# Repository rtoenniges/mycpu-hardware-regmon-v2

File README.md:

# MyCPU_HDW_RegMonV2
A hardware expansion for for the [MyCPU](http://www.mycpu.eu/) from Dennis Kuschel to display the various CPU internal registers.

#### Attention: 
**This project especially the layouts are not yet finished and have _never been tested!_
So be careful if you connect this to your MyCPU!**

## Features
- Values display in Hex using an EPROM to convert Binary to 7-segment
- Hold CPU on a specific address using DIP-Switches
- You dont have to build the whole Monitor - Its split into 3x Driver and 2x Monitor modules

## Registers
- Accu
- X-Reg
- Y-Reg
- Stackpointer
- OP-Code
- ALU-Reg 1
- ALU-Reg 2
- ALU-OUT
- Sign-, Zero-, Carry-Flag
- Program Counter
- Addressregister

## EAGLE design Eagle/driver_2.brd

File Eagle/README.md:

# Hardware (Drivers and Monitors)
The hardware is each splitted into two modules (Driver and Monitor).
The two modules where connected by a ribbon cable which should not be too long.

## Driver 1 (Program Counter) -> Monitor 12
Driver 1 is for the Program Counter and have to be placed between the Signal Decoder- and the Program Counter-Board.

You have to remove IC44 and IC46 from the Program-Counter-Board and place it on the Driver 1-Board and use IC socket extensions to connect the ICs again to the Programm Counter-Board like the Memory-Base-, and the Memory-Extension-Board.

You can connect the Monitor 12-Board to display the Programm Counter value.

## Driver 2 (Address Bus) -> Monitor 12, AddressHold
Driver 2 is for the Address Bus and have to be placed between the Program Counter- and the Bus Interface-Board

You can connect the Monitor 12-Board to display the Address Bus value and with the AddressHold-Board you can select an address with dip-switches to hold the CPU on a specific point.

## Driver 3 (Accu, X, Y, SP, OP, AR1, AR2, ALU, O-, V-, C-Flag) -> Monitor 3
Driver 3 is for the various internal CPU register and have to be placed between the Microcode Control- and the Signal Decoder-Board.

You can connect the Monitor 3-Board to display all the registers and flags.

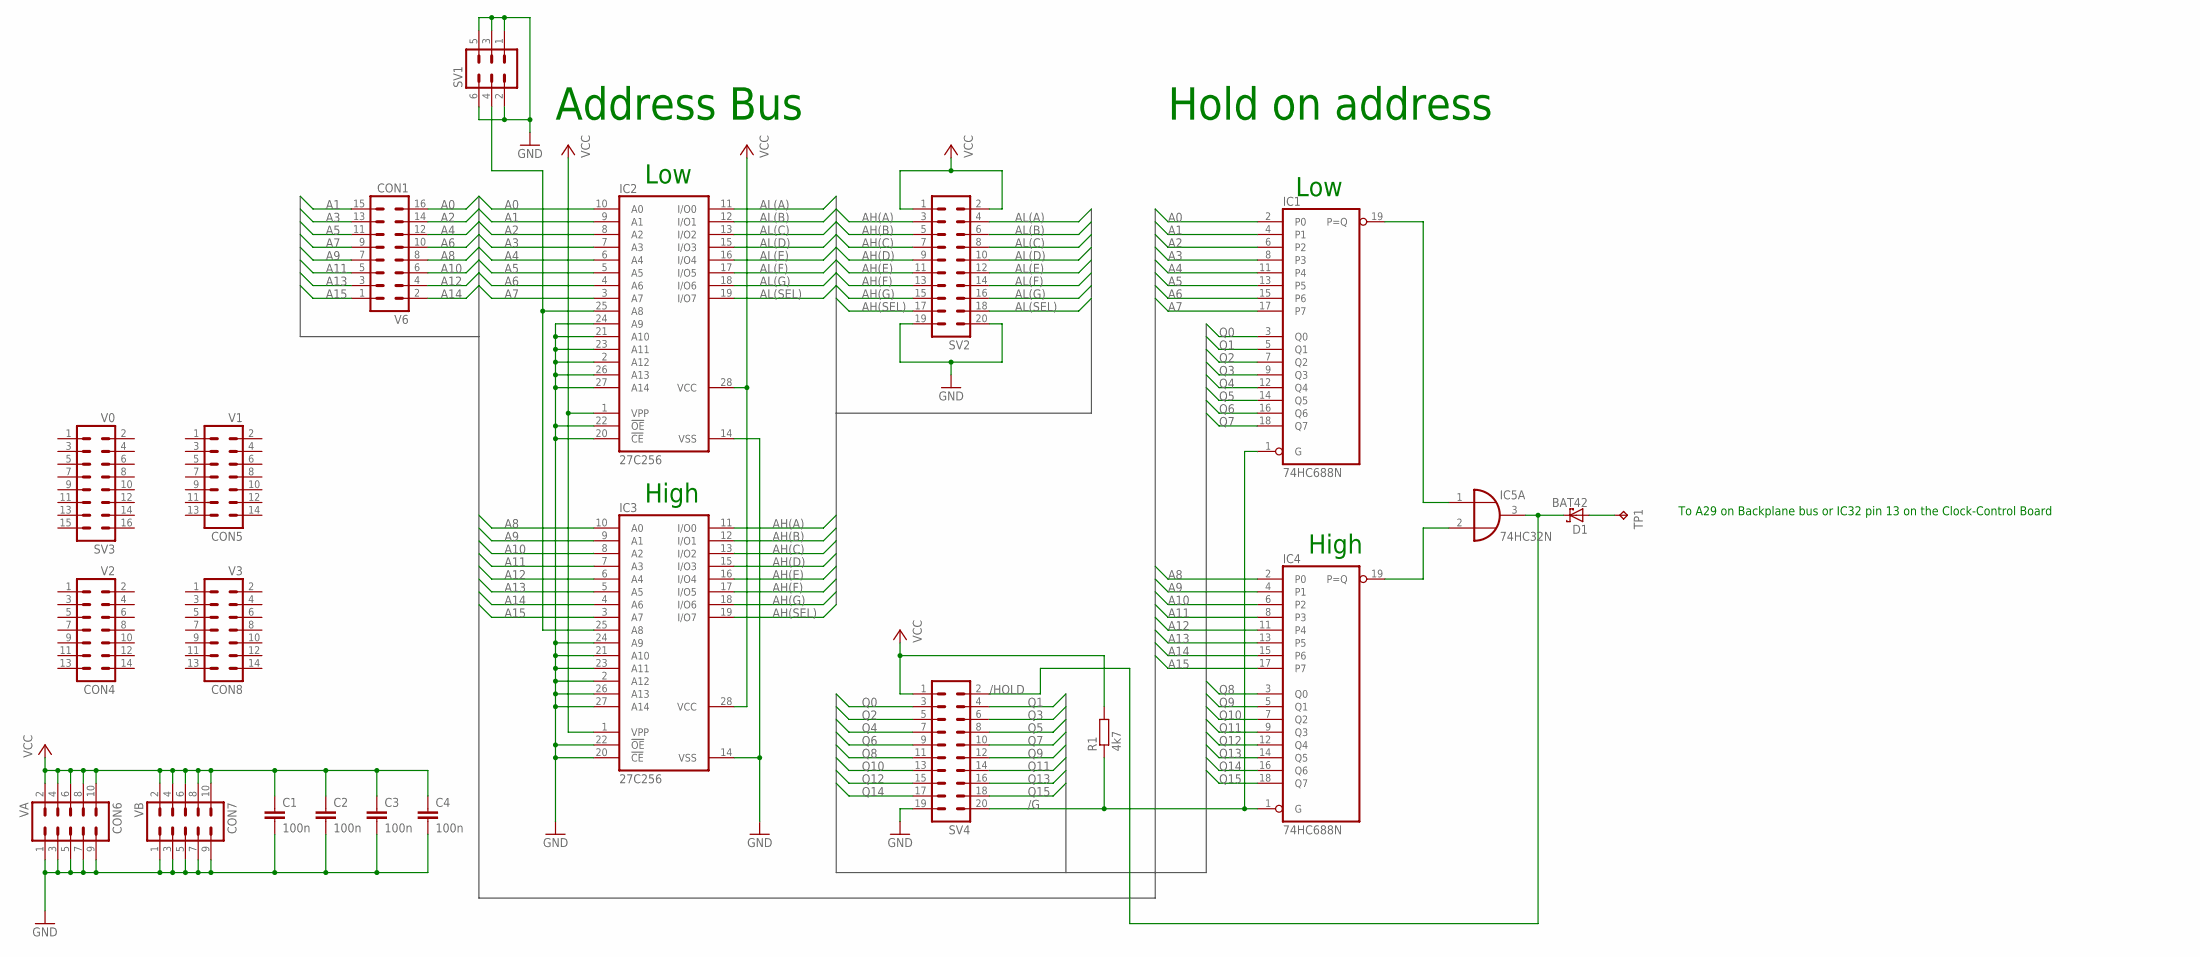
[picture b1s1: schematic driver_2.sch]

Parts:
C1, C2, C3, C4: 100n; C050-024X044
CON1: V6; ML16
CON4: V2; ML14
CON5: V1; ML14
CON6: VA; ML10
CON7: VB; ML10
CON8: V3; ML14
D1: BAT42; DO35-10
IC1, IC4: 74HC688N; DIL20
IC2, IC3: 27C256; DIL28-6
IC5: 74HC32N; DIL14
R1: 4k7; 0204/5
SV1: ML6
SV2, SV4: ML20L
SV3: V0; ML16
TP1: Interface -> R12; P1-17

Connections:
/G: IC1.1 (G), IC4.1 (G), R1.1, SV4.20
/HOLD: D1.C, IC5.3 (O), SV4.2
A0: CON1.16, IC1.2 (P0), IC2.10 (A0)
A1: CON1.15, IC1.4 (P1), IC2.9 (A1)
A2: CON1.14, IC1.6 (P2), IC2.8 (A2)
A3: CON1.13, IC1.8 (P3), IC2.7 (A3)
A4: CON1.12, IC1.11 (P4), IC2.6 (A4)
A5: CON1.11, IC1.13 (P5), IC2.5 (A5)
A6: CON1.10, IC1.15 (P6), IC2.4 (A6)
A7: CON1.9, IC1.17 (P7), IC2.3 (A7)
A8: CON1.8, IC3.10 (A0), IC4.2 (P0)
A9: CON1.7, IC3.9 (A1), IC4.4 (P1)
A10: CON1.6, IC3.8 (A2), IC4.6 (P2)
A11: CON1.5, IC3.7 (A3), IC4.8 (P3)
A12: CON1.4, IC3.6 (A4), IC4.11 (P4)
A13: CON1.3, IC3.5 (A5), IC4.13 (P5)
A14: CON1.2, IC3.4 (A6), IC4.15 (P6)
A15: CON1.1, IC3.3 (A7), IC4.17 (P7)
AH(A): IC3.11 (I/O0), SV2.3
AH(B): IC3.12 (I/O1), SV2.5
AH(C): IC3.13 (I/O2), SV2.7
AH(D): IC3.15 (I/O3), SV2.9
AH(E): IC3.16 (I/O4), SV2.11
AH(F): IC3.17 (I/O5), SV2.13
AH(G): IC3.18 (I/O6), SV2.15
AH(SEL): IC3.19 (I/O7), SV2.17
AL(A): IC2.11 (I/O0), SV2.4
AL(B): IC2.12 (I/O1), SV2.6
AL(C): IC2.13 (I/O2), SV2.8
AL(D): IC2.15 (I/O3), SV2.10
AL(E): IC2.16 (I/O4), SV2.12
AL(F): IC2.17 (I/O5), SV2.14
AL(G): IC2.18 (I/O6), SV2.16
AL(SEL): IC2.19 (I/O7), SV2.18
GND: C1.2, C2.2, C3.2, C4.2, CON6.1, CON6.3, CON6.5, CON6.7, CON6.9, CON7.1, CON7.3, CON7.5, CON7.7, CON7.9, IC1.10 (GND), IC2.2 (A12), IC2.14 (VSS), IC2.20 (!CE), IC2.21 (A10), IC2.22 (!OE), IC2.23 (A11), IC2.24 (A9), IC2.26 (A13), IC2.27 (A14), IC3.2 (A12), IC3.14 (VSS), IC3.20 (!CE), IC3.21 (A10), IC3.22 (!OE), IC3.23 (A11), IC3.24 (A9), IC3.26 (A13), IC3.27 (A14), IC4.10 (GND), IC5.7 (GND), SV1.1, SV1.2, SV1.3, SV1.5, SV1.6, SV2.19, SV2.20, SV4.19
unnamed: IC2.25 (A8), IC3.25 (A8), SV1.4
unnamed: IC1.19 (P=Q), IC5.1 (I0)
unnamed: IC4.19 (P=Q), IC5.2 (I1)
unnamed: D1.A, TP1.TP
Q0: IC1.3 (Q0), SV4.3
Q1: IC1.5 (Q1), SV4.4
Q2: IC1.7 (Q2), SV4.5
Q3: IC1.9 (Q3), SV4.6
Q4: IC1.12 (Q4), SV4.7
Q5: IC1.14 (Q5), SV4.8
Q6: IC1.16 (Q6), SV4.9
Q7: IC1.18 (Q7), SV4.10
Q8: IC4.3 (Q0), SV4.11
Q9: IC4.5 (Q1), SV4.12
Q10: IC4.7 (Q2), SV4.13
Q11: IC4.9 (Q3), SV4.14
Q12: IC4.12 (Q4), SV4.15
Q13: IC4.14 (Q5), SV4.16
Q14: IC4.16 (Q6), SV4.17
Q15: IC4.18 (Q7), SV4.18
VCC: C1.1, C2.1, C3.1, C4.1, CON6.2, CON6.4, CON6.6, CON6.8, CON6.10, CON7.2, CON7.4, CON7.6, CON7.8, CON7.10, IC1.20 (VCC), IC2.1 (VPP), IC2.28 (VCC), IC3.1 (VPP), IC3.28 (VCC), IC4.20 (VCC), IC5.14 (VCC), R1.2, SV2.1, SV2.2, SV4.1

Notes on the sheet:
Address Bus
Low
High
Hold on address
To A29 on Backplane bus or IC32 pin 13 on the Clock-Control Board

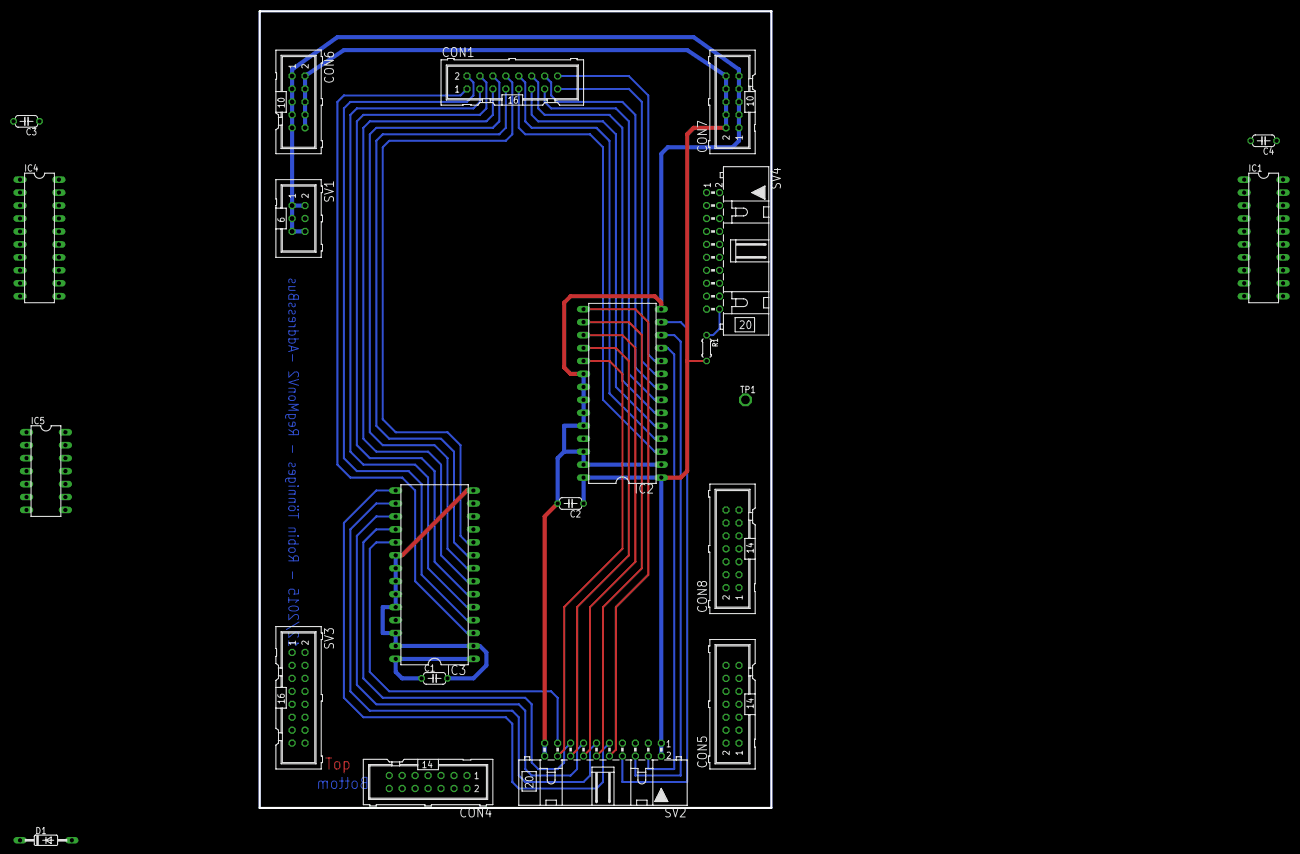
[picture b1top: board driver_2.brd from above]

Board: 2 copper layers, 100.3 x 156.2 mm, 22 parts (0 on the bottom side), 56 nets.

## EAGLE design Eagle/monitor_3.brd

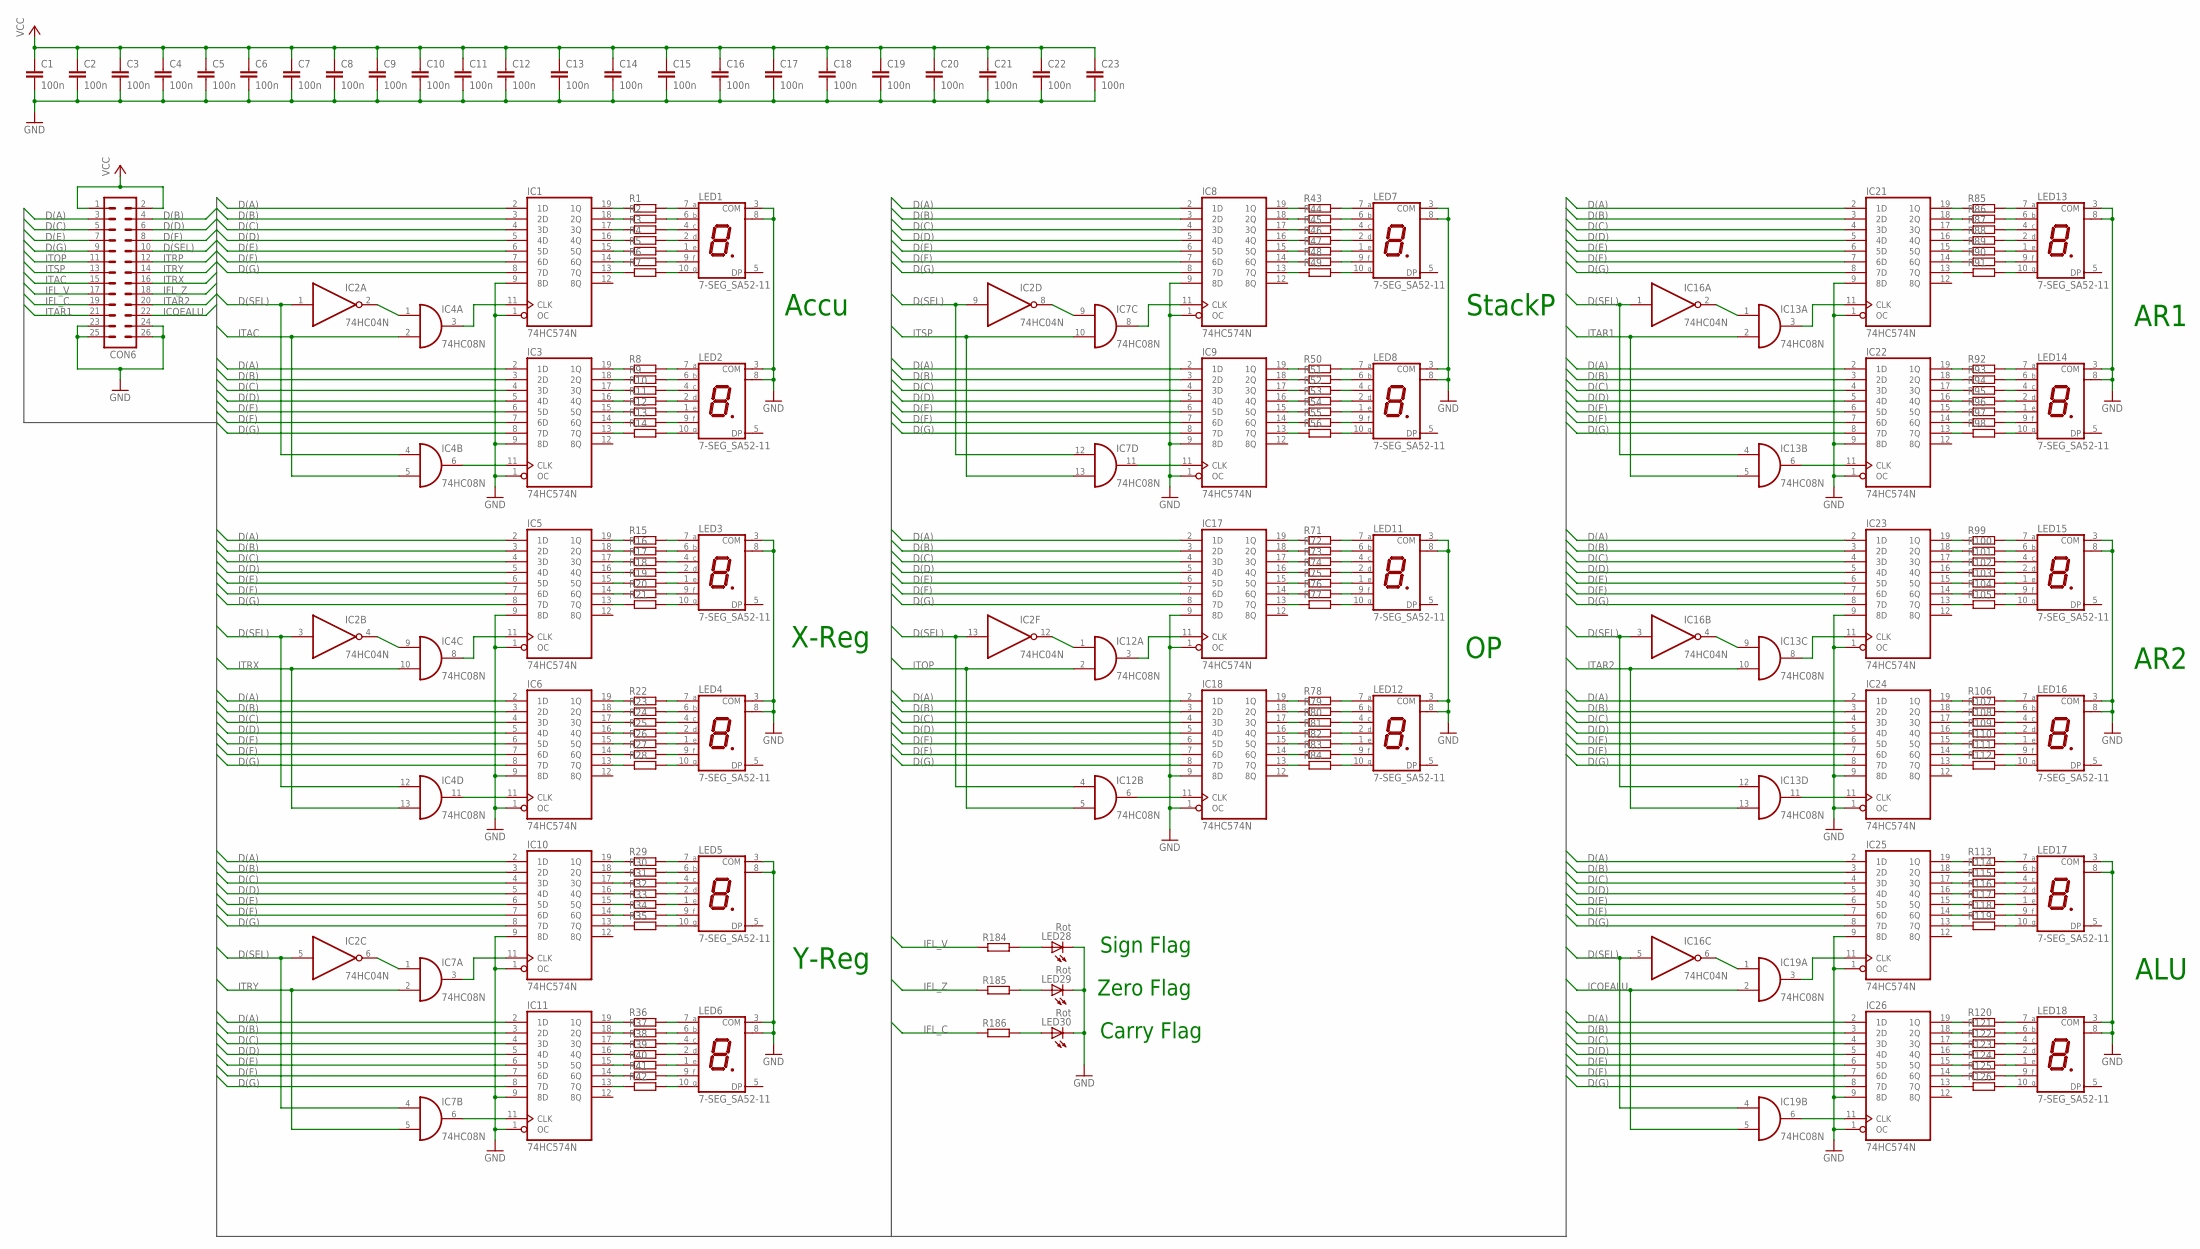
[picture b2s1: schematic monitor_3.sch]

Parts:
C1, C2, C3, C4, C5, C6, C7, C8, C9, C10, C11, C12, C13, C14, C15, C16, C17, C18, C19, C20, C21, C22, C23: 100n; C025-024X044
CON6: ML26L
IC1, IC3, IC5, IC6, IC8, IC9, IC10, IC11, IC17, IC18, IC21, IC22, IC23, IC24, IC25, IC26: 74HC574N; DIL20
IC2, IC16: 74HC04N; DIL14
IC4, IC7, IC12, IC13, IC19: 74HC08N; DIL14
LED1, LED2, LED3, LED4, LED5, LED6, LED7, LED8, LED11, LED12, LED13, LED14, LED15, LED16, LED17, LED18: 7-SEG_SA52-11; SA52-11
LED28, LED29, LED30: Rot; LED5MM
R1, R2, R3, R4, R5, R6, R7, R8, R9, R10, R11, R12, R13, R14, R15, R16, R17, R18, R19, R20, R21, R22, R23, R24, R25, R26, R27, R28, R29, R30, R31, R32, R33, R34, R35, R36, R37, R38, R39, R40, R41, R42, R43, R44, R45, R46, R47, R48, R49, R50, R51, R52, R53, R54, R55, R56, R71, R72, R73, R74, R75, R76, R77, R78, R79, R80, R81, R82, R83, R84, R85, R86, R87, R88, R89, R90, R91, R92, R93, R94, R95, R96, R97, R98, R99, R100, R101, R102, R103, R104, R105, R106, R107, R108, R109, R110, R111, R112, R113, R114, R115, R116, R117, R118, R119, R120, R121, R122, R123, R124, R125, R126, R184, R185, R186: R-EU_0207/7; 0207/7

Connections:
D(A): CON6.3, IC1.2 (1D), IC3.2 (1D), IC5.2 (1D), IC6.2 (1D), IC8.2 (1D), IC9.2 (1D), IC10.2 (1D), IC11.2 (1D), IC17.2 (1D), IC18.2 (1D), IC21.2 (1D), IC22.2 (1D), IC23.2 (1D), IC24.2 (1D), IC25.2 (1D), IC26.2 (1D)
D(B): CON6.4, IC1.3 (2D), IC3.3 (2D), IC5.3 (2D), IC6.3 (2D), IC8.3 (2D), IC9.3 (2D), IC10.3 (2D), IC11.3 (2D), IC17.3 (2D), IC18.3 (2D), IC21.3 (2D), IC22.3 (2D), IC23.3 (2D), IC24.3 (2D), IC25.3 (2D), IC26.3 (2D)
D(C): CON6.5, IC1.4 (3D), IC3.4 (3D), IC5.4 (3D), IC6.4 (3D), IC8.4 (3D), IC9.4 (3D), IC10.4 (3D), IC11.4 (3D), IC17.4 (3D), IC18.4 (3D), IC21.4 (3D), IC22.4 (3D), IC23.4 (3D), IC24.4 (3D), IC25.4 (3D), IC26.4 (3D)
D(D): CON6.6, IC1.5 (4D), IC3.5 (4D), IC5.5 (4D), IC6.5 (4D), IC8.5 (4D), IC9.5 (4D), IC10.5 (4D), IC11.5 (4D), IC17.5 (4D), IC18.5 (4D), IC21.5 (4D), IC22.5 (4D), IC23.5 (4D), IC24.5 (4D), IC25.5 (4D), IC26.5 (4D)
D(E): CON6.7, IC1.6 (5D), IC3.6 (5D), IC5.6 (5D), IC6.6 (5D), IC8.6 (5D), IC9.6 (5D), IC10.6 (5D), IC11.6 (5D), IC17.6 (5D), IC18.6 (5D), IC21.6 (5D), IC22.6 (5D), IC23.6 (5D), IC24.6 (5D), IC25.6 (5D), IC26.6 (5D)
D(F): CON6.8, IC1.7 (6D), IC3.7 (6D), IC5.7 (6D), IC6.7 (6D), IC8.7 (6D), IC9.7 (6D), IC10.7 (6D), IC11.7 (6D), IC17.7 (6D), IC18.7 (6D), IC21.7 (6D), IC22.7 (6D), IC23.7 (6D), IC24.7 (6D), IC25.7 (6D), IC26.7 (6D)
D(G): CON6.9, IC1.8 (7D), IC3.8 (7D), IC5.8 (7D), IC6.8 (7D), IC8.8 (7D), IC9.8 (7D), IC10.8 (7D), IC11.8 (7D), IC17.8 (7D), IC18.8 (7D), IC21.8 (7D), IC22.8 (7D), IC23.8 (7D), IC24.8 (7D), IC25.8 (7D), IC26.8 (7D)
D(SEL): CON6.10, IC2.1 (I), IC2.3 (I), IC2.5 (I), IC2.9 (I), IC2.13 (I), IC4.4 (I0), IC4.12 (I0), IC7.4 (I0), IC7.12 (I0), IC12.4 (I0), IC13.4 (I0), IC13.12 (I0), IC16.1 (I), IC16.3 (I), IC16.5 (I), IC19.4 (I0)
GND: C1.2, C2.2, C3.2, C4.2, C5.2, C6.2, C7.2, C8.2, C9.2, C10.2, C11.2, C12.2, C13.2, C14.2, C15.2, C16.2, C17.2, C18.2, C19.2, C20.2, C21.2, C22.2, C23.2, CON6.23, CON6.24, CON6.25, CON6.26, IC1.1 (OC), IC1.9 (8D), IC1.10 (GND), IC2.7 (GND), IC3.1 (OC), IC3.9 (8D), IC3.10 (GND), IC4.7 (GND), IC5.1 (OC), IC5.9 (8D), IC5.10 (GND), IC6.1 (OC), IC6.9 (8D), IC6.10 (GND), IC7.7 (GND), IC8.1 (OC), IC8.9 (8D), IC8.10 (GND), IC9.1 (OC), IC9.9 (8D), IC9.10 (GND), IC10.1 (OC), IC10.9 (8D), IC10.10 (GND), IC11.1 (OC), IC11.9 (8D), IC11.10 (GND), IC12.7 (GND), IC13.7 (GND), IC16.7 (GND), IC17.1 (OC), IC17.9 (8D), IC17.10 (GND), IC18.1 (OC), IC18.9 (8D), IC18.10 (GND), IC19.7 (GND), IC21.1 (OC), IC21.9 (8D), IC21.10 (GND), IC22.1 (OC), IC22.9 (8D), IC22.10 (GND), IC23.1 (OC), IC23.9 (8D), IC23.10 (GND), IC24.1 (OC), IC24.9 (8D), IC24.10 (GND), IC25.1 (OC), IC25.9 (8D), IC25.10 (GND), IC26.1 (OC), IC26.9 (8D), IC26.10 (GND), LED1.3 (COM), LED1.8 (COM), LED2.3 (COM), LED2.8 (COM), LED3.3 (COM), LED3.8 (COM), LED4.3 (COM), LED4.8 (COM), LED5.3 (COM), LED5.8 (COM), LED6.3 (COM), LED6.8 (COM), LED7.3 (COM), LED7.8 (COM), LED8.3 (COM), LED8.8 (COM), LED11.3 (COM), LED11.8 (COM), LED12.3 (COM), LED12.8 (COM), LED13.3 (COM), LED13.8 (COM), LED14.3 (COM), LED14.8 (COM), LED15.3 (COM), LED15.8 (COM), LED16.3 (COM), LED16.8 (COM), LED17.3 (COM), LED17.8 (COM), LED18.3 (COM), LED18.8 (COM), LED28.K (C), LED29.K (C), LED30.K (C)
ICOEALU: CON6.22, IC19.2 (I1), IC19.5 (I1)
IFL_C: CON6.19, R186.1
IFL_V: CON6.17, R184.1
IFL_Z: CON6.18, R185.1
ITAC: CON6.15, IC4.2 (I1), IC4.5 (I1)
ITAR1: CON6.21, IC13.2 (I1), IC13.5 (I1)
ITAR2: CON6.20, IC13.10 (I1), IC13.13 (I1)
ITOP: CON6.11, IC12.2 (I1), IC12.5 (I1)
ITRP: CON6.12
ITRX: CON6.16, IC4.10 (I1), IC4.13 (I1)
ITRY: CON6.14, IC7.2 (I1), IC7.5 (I1)
ITSP: CON6.13, IC7.10 (I1), IC7.13 (I1)
unnamed: IC2.2 (O), IC4.1 (I0)
unnamed: IC1.11 (CLK), IC4.3 (O)
unnamed: LED1.6 (B), R2.2
unnamed: IC1.19 (1Q), R1.1
unnamed: IC1.18 (2Q), R2.1
unnamed: IC1.17 (3Q), R3.1
unnamed: IC1.16 (4Q), R4.1
unnamed: IC1.15 (5Q), R5.1
unnamed: IC1.14 (6Q), R6.1
unnamed: IC1.13 (7Q), R7.1
unnamed: LED1.7 (A), R1.2
unnamed: LED1.4 (C), R3.2
unnamed: LED1.2 (D), R4.2
unnamed: LED1.1 (E), R5.2
unnamed: LED1.9 (F), R6.2
unnamed: LED1.10 (G), R7.2
unnamed: IC3.11 (CLK), IC4.6 (O)
unnamed: LED2.6 (B), R9.2
unnamed: IC3.19 (1Q), R8.1
unnamed: IC3.18 (2Q), R9.1
unnamed: IC3.17 (3Q), R10.1
unnamed: IC3.16 (4Q), R11.1
unnamed: IC3.15 (5Q), R12.1
unnamed: IC3.14 (6Q), R13.1
unnamed: IC3.13 (7Q), R14.1
unnamed: LED2.7 (A), R8.2
unnamed: LED2.4 (C), R10.2
unnamed: LED2.2 (D), R11.2
unnamed: LED2.1 (E), R12.2
unnamed: LED2.9 (F), R13.2
unnamed: LED2.10 (G), R14.2
unnamed: IC2.4 (O), IC4.9 (I0)
unnamed: IC4.8 (O), IC5.11 (CLK)
unnamed: IC4.11 (O), IC6.11 (CLK)
unnamed: LED3.6 (B), R16.2
unnamed: IC5.19 (1Q), R15.1
unnamed: IC5.18 (2Q), R16.1
unnamed: IC5.17 (3Q), R17.1
unnamed: IC5.16 (4Q), R18.1
unnamed: IC5.15 (5Q), R19.1
unnamed: IC5.14 (6Q), R20.1
unnamed: IC5.13 (7Q), R21.1
unnamed: LED3.7 (A), R15.2
unnamed: LED3.4 (C), R17.2
unnamed: LED3.2 (D), R18.2
unnamed: LED3.1 (E), R19.2
unnamed: LED3.9 (F), R20.2
unnamed: LED3.10 (G), R21.2
unnamed: IC2.6 (O), IC7.1 (I0)
unnamed: IC7.3 (O), IC10.11 (CLK)
unnamed: IC7.6 (O), IC11.11 (CLK)
unnamed: LED7.6 (B), R44.2
unnamed: IC8.19 (1Q), R43.1
unnamed: IC8.18 (2Q), R44.1
unnamed: IC8.17 (3Q), R45.1
unnamed: IC8.16 (4Q), R46.1
unnamed: IC8.15 (5Q), R47.1
unnamed: IC8.14 (6Q), R48.1
unnamed: IC8.13 (7Q), R49.1
unnamed: LED7.7 (A), R43.2
unnamed: LED7.4 (C), R45.2
unnamed: LED7.2 (D), R46.2
unnamed: LED7.1 (E), R47.2
unnamed: LED7.9 (F), R48.2
unnamed: LED7.10 (G), R49.2
unnamed: IC2.8 (O), IC7.9 (I0)
unnamed: IC7.8 (O), IC8.11 (CLK)
unnamed: IC7.11 (O), IC9.11 (CLK)
unnamed: LED8.6 (B), R51.2
unnamed: IC9.19 (1Q), R50.1
unnamed: IC9.18 (2Q), R51.1
unnamed: IC9.17 (3Q), R52.1
unnamed: IC9.16 (4Q), R53.1
unnamed: IC9.15 (5Q), R54.1
unnamed: IC9.14 (6Q), R55.1
unnamed: IC9.13 (7Q), R56.1
unnamed: LED8.7 (A), R50.2
unnamed: LED8.4 (C), R52.2
unnamed: LED8.2 (D), R53.2
unnamed: LED8.1 (E), R54.2
unnamed: LED8.9 (F), R55.2
unnamed: LED8.10 (G), R56.2
unnamed: IC2.12 (O), IC12.1 (I0)
unnamed: IC12.3 (O), IC17.11 (CLK)
unnamed: IC12.6 (O), IC18.11 (CLK)
unnamed: LED13.6 (B), R86.2
unnamed: IC21.19 (1Q), R85.1
unnamed: IC21.18 (2Q), R86.1
unnamed: IC21.17 (3Q), R87.1
unnamed: IC21.16 (4Q), R88.1
unnamed: IC21.15 (5Q), R89.1
unnamed: IC21.14 (6Q), R90.1
unnamed: IC21.13 (7Q), R91.1
unnamed: LED13.7 (A), R85.2
unnamed: LED13.4 (C), R87.2
unnamed: LED13.2 (D), R88.2
unnamed: LED13.1 (E), R89.2
unnamed: LED13.9 (F), R90.2
unnamed: LED13.10 (G), R91.2
unnamed: IC13.1 (I0), IC16.2 (O)
unnamed: IC13.3 (O), IC21.11 (CLK)
unnamed: IC13.6 (O), IC22.11 (CLK)
unnamed: LED14.6 (B), R93.2
unnamed: IC22.19 (1Q), R92.1
unnamed: IC22.18 (2Q), R93.1
unnamed: IC22.17 (3Q), R94.1
unnamed: IC22.16 (4Q), R95.1
unnamed: IC22.15 (5Q), R96.1
unnamed: IC22.14 (6Q), R97.1
unnamed: IC22.13 (7Q), R98.1
unnamed: LED14.7 (A), R92.2
unnamed: LED14.4 (C), R94.2
unnamed: LED14.2 (D), R95.2
unnamed: LED14.1 (E), R96.2
unnamed: LED14.9 (F), R97.2
unnamed: LED14.10 (G), R98.2
unnamed: IC13.9 (I0), IC16.4 (O)
unnamed: IC13.8 (O), IC23.11 (CLK)
unnamed: IC13.11 (O), IC24.11 (CLK)
unnamed: LED15.6 (B), R100.2
unnamed: IC23.19 (1Q), R99.1
unnamed: IC23.18 (2Q), R100.1
unnamed: IC23.17 (3Q), R101.1
unnamed: IC23.16 (4Q), R102.1
unnamed: IC23.15 (5Q), R103.1
unnamed: IC23.14 (6Q), R104.1
unnamed: IC23.13 (7Q), R105.1
unnamed: LED15.7 (A), R99.2
unnamed: LED15.4 (C), R101.2
unnamed: LED15.2 (D), R102.2
unnamed: LED15.1 (E), R103.2
unnamed: LED15.9 (F), R104.2
unnamed: LED15.10 (G), R105.2
unnamed: IC16.6 (O), IC19.1 (I0)
unnamed: IC19.3 (O), IC25.11 (CLK)
unnamed: IC19.6 (O), IC26.11 (CLK)
unnamed: LED4.6 (B), R23.2
unnamed: IC6.19 (1Q), R22.1
unnamed: IC6.18 (2Q), R23.1
unnamed: IC6.17 (3Q), R24.1
unnamed: IC6.16 (4Q), R25.1
unnamed: IC6.15 (5Q), R26.1
unnamed: IC6.14 (6Q), R27.1
unnamed: IC6.13 (7Q), R28.1
unnamed: LED4.7 (A), R22.2
unnamed: LED4.4 (C), R24.2
unnamed: LED4.2 (D), R25.2
unnamed: LED4.1 (E), R26.2
unnamed: LED4.9 (F), R27.2
unnamed: LED4.10 (G), R28.2
unnamed: LED5.6 (B), R30.2
unnamed: IC10.19 (1Q), R29.1
unnamed: IC10.18 (2Q), R30.1
unnamed: IC10.17 (3Q), R31.1
unnamed: IC10.16 (4Q), R32.1
unnamed: IC10.15 (5Q), R33.1
unnamed: IC10.14 (6Q), R34.1
unnamed: IC10.13 (7Q), R35.1
unnamed: LED5.7 (A), R29.2
unnamed: LED5.4 (C), R31.2
unnamed: LED5.2 (D), R32.2
unnamed: LED5.1 (E), R33.2
unnamed: LED5.9 (F), R34.2
unnamed: LED5.10 (G), R35.2
unnamed: LED6.6 (B), R37.2
unnamed: IC11.19 (1Q), R36.1
unnamed: IC11.18 (2Q), R37.1
unnamed: IC11.17 (3Q), R38.1
unnamed: IC11.16 (4Q), R39.1
unnamed: IC11.15 (5Q), R40.1
unnamed: IC11.14 (6Q), R41.1
unnamed: IC11.13 (7Q), R42.1
unnamed: LED6.7 (A), R36.2
unnamed: LED6.4 (C), R38.2
unnamed: LED6.2 (D), R39.2
unnamed: LED6.1 (E), R40.2
unnamed: LED6.9 (F), R41.2
unnamed: LED6.10 (G), R42.2
unnamed: LED11.6 (B), R72.2
unnamed: IC17.19 (1Q), R71.1
unnamed: IC17.18 (2Q), R72.1
unnamed: IC17.17 (3Q), R73.1
unnamed: IC17.16 (4Q), R74.1
unnamed: IC17.15 (5Q), R75.1
unnamed: IC17.14 (6Q), R76.1
unnamed: IC17.13 (7Q), R77.1
unnamed: LED11.7 (A), R71.2
unnamed: LED11.4 (C), R73.2
unnamed: LED11.2 (D), R74.2
unnamed: LED11.1 (E), R75.2
unnamed: LED11.9 (F), R76.2
unnamed: LED11.10 (G), R77.2
unnamed: LED12.6 (B), R79.2
unnamed: IC18.19 (1Q), R78.1
unnamed: IC18.18 (2Q), R79.1
unnamed: IC18.17 (3Q), R80.1
unnamed: IC18.16 (4Q), R81.1
unnamed: IC18.15 (5Q), R82.1
unnamed: IC18.14 (6Q), R83.1
unnamed: IC18.13 (7Q), R84.1
unnamed: LED12.7 (A), R78.2
unnamed: LED12.4 (C), R80.2
unnamed: LED12.2 (D), R81.2
unnamed: LED12.1 (E), R82.2
unnamed: LED12.9 (F), R83.2
unnamed: LED12.10 (G), R84.2
unnamed: LED16.6 (B), R107.2
unnamed: IC24.19 (1Q), R106.1
unnamed: IC24.18 (2Q), R107.1
unnamed: IC24.17 (3Q), R108.1
unnamed: IC24.16 (4Q), R109.1
unnamed: IC24.15 (5Q), R110.1
unnamed: IC24.14 (6Q), R111.1
unnamed: IC24.13 (7Q), R112.1
unnamed: LED16.7 (A), R106.2
unnamed: LED16.4 (C), R108.2
unnamed: LED16.2 (D), R109.2
unnamed: LED16.1 (E), R110.2
unnamed: LED16.9 (F), R111.2
unnamed: LED16.10 (G), R112.2
unnamed: LED17.6 (B), R114.2
unnamed: IC25.19 (1Q), R113.1
unnamed: IC25.18 (2Q), R114.1
unnamed: IC25.17 (3Q), R115.1
unnamed: IC25.16 (4Q), R116.1
unnamed: IC25.15 (5Q), R117.1
unnamed: IC25.14 (6Q), R118.1
unnamed: IC25.13 (7Q), R119.1
unnamed: LED17.7 (A), R113.2
unnamed: LED17.4 (C), R115.2
unnamed: LED17.2 (D), R116.2
unnamed: LED17.1 (E), R117.2
unnamed: LED17.9 (F), R118.2
unnamed: LED17.10 (G), R119.2
unnamed: LED18.6 (B), R121.2
unnamed: IC26.19 (1Q), R120.1
unnamed: IC26.18 (2Q), R121.1
unnamed: IC26.17 (3Q), R122.1
unnamed: IC26.16 (4Q), R123.1
unnamed: IC26.15 (5Q), R124.1
unnamed: IC26.14 (6Q), R125.1
unnamed: IC26.13 (7Q), R126.1
unnamed: LED18.7 (A), R120.2
unnamed: LED18.4 (C), R122.2
unnamed: LED18.2 (D), R123.2
unnamed: LED18.1 (E), R124.2
unnamed: LED18.9 (F), R125.2
unnamed: LED18.10 (G), R126.2
unnamed: LED28.A, R184.2
unnamed: LED29.A, R185.2
unnamed: LED30.A, R186.2
VCC: C1.1, C2.1, C3.1, C4.1, C5.1, C6.1, C7.1, C8.1, C9.1, C10.1, C11.1, C12.1, C13.1, C14.1, C15.1, C16.1, C17.1, C18.1, C19.1, C20.1, C21.1, C22.1, C23.1, CON6.1, CON6.2, IC1.20 (VCC), IC2.14 (VCC), IC3.20 (VCC), IC4.14 (VCC), IC5.20 (VCC), IC6.20 (VCC), IC7.14 (VCC), IC8.20 (VCC), IC9.20 (VCC), IC10.20 (VCC), IC11.20 (VCC), IC12.14 (VCC), IC13.14 (VCC), IC16.14 (VCC), IC17.20 (VCC), IC18.20 (VCC), IC19.14 (VCC), IC21.20 (VCC), IC22.20 (VCC), IC23.20 (VCC), IC24.20 (VCC), IC25.20 (VCC), IC26.20 (VCC)

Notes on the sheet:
Accu
X-Reg
Y-Reg
StackP
AR1
AR2
ALU
Sign Flag
Zero Flag
Carry Flag

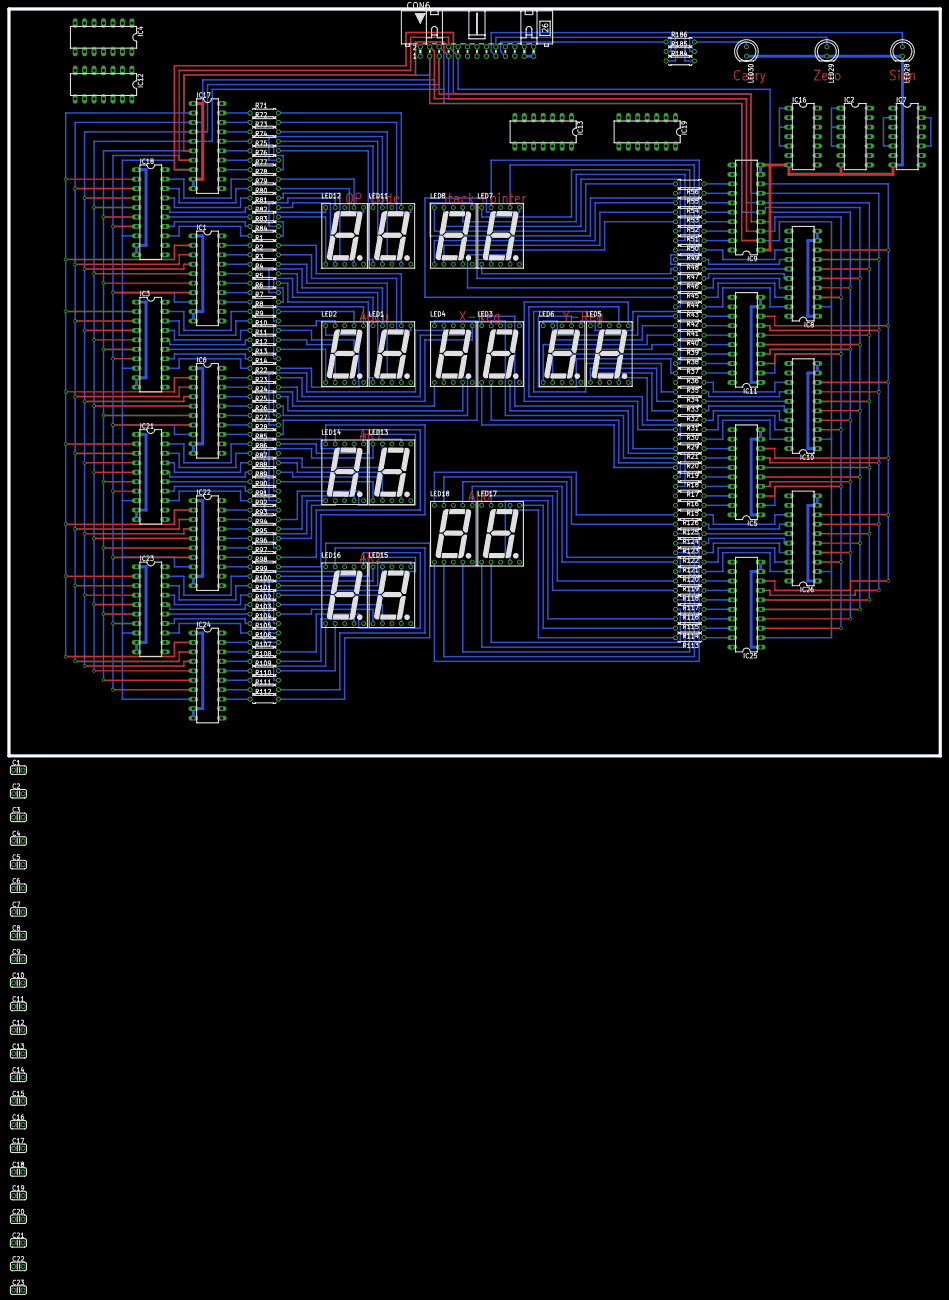
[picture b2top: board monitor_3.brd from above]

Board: 2 copper layers, 250.2 x 200.7 mm, 181 parts (0 on the bottom side), 272 nets.

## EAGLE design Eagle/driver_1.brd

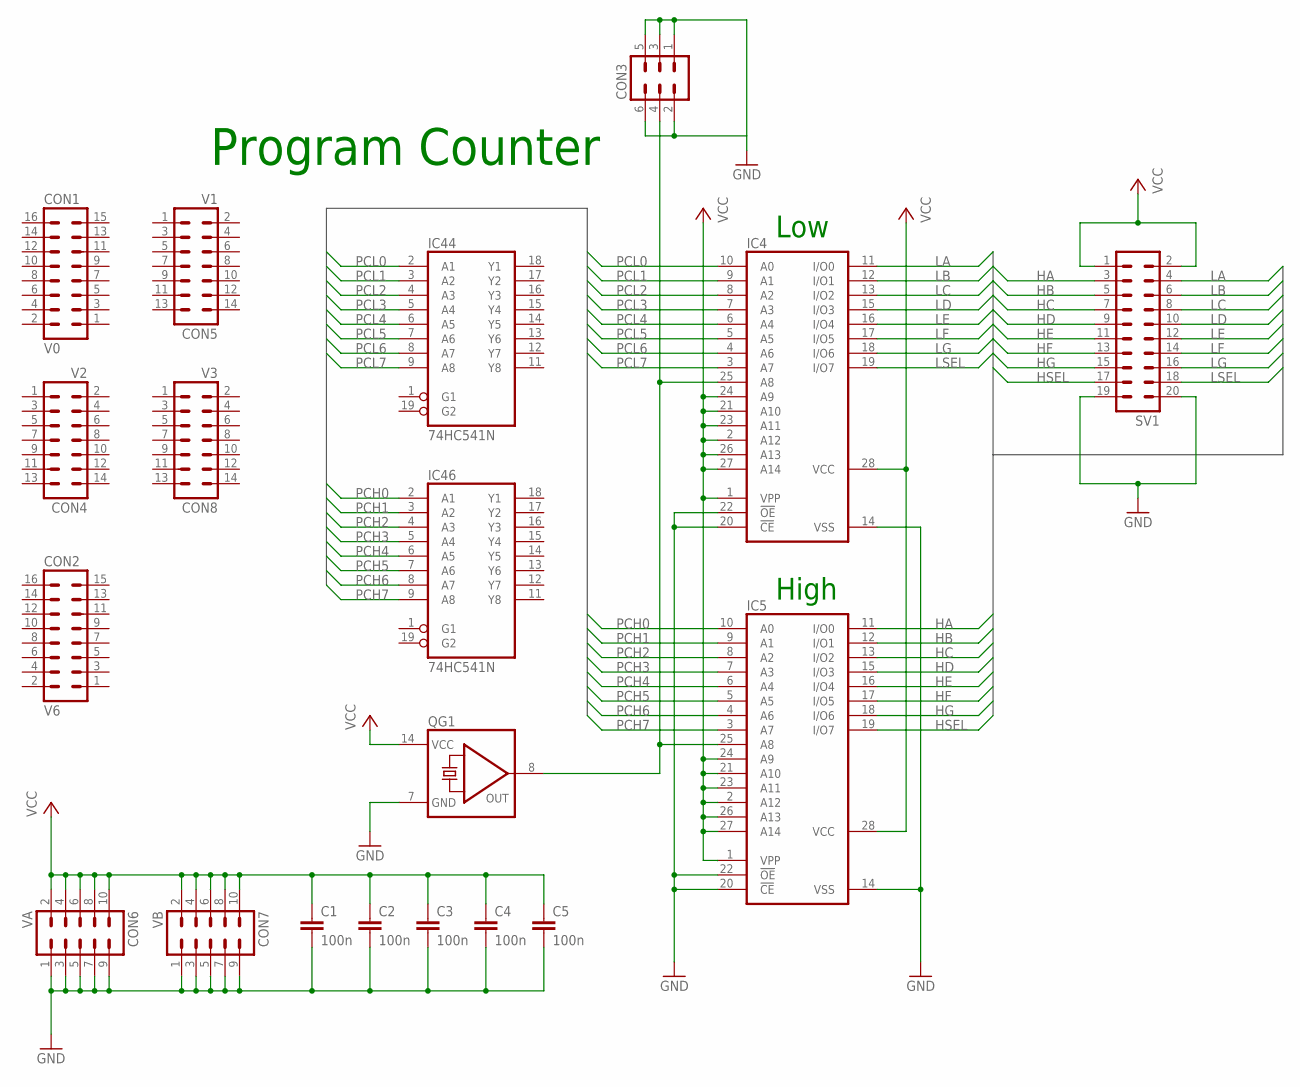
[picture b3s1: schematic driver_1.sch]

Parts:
C1, C2, C3, C4, C5: 100n; C050-024X044
CON1: V0; ML16
CON2: V6; ML16
CON3: ML6
CON4: V2; ML14
CON5: V1; ML14
CON6: VA; ML10
CON7: VB; ML10
CON8: V3; ML14
IC4, IC5: 27C256AG; DIL28-6
IC44, IC46: 74HC541N; DIL20
QG1: QG5860; DIL14S
SV1: ML20L

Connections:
GND: C1.2, C2.2, C3.2, C4.2, C5.2, CON3.1, CON3.2, CON3.3, CON3.5, CON3.6, CON6.1, CON6.3, CON6.5, CON6.7, CON6.9, CON7.1, CON7.3, CON7.5, CON7.7, CON7.9, IC4.14 (VSS), IC4.20 (!CE), IC4.22 (!OE), IC5.14 (VSS), IC5.20 (!CE), IC5.22 (!OE), IC44.10 (GND), IC46.10 (GND), QG1.7 (GND), SV1.19, SV1.20
HA: IC5.11 (I/O0), SV1.3
HB: IC5.12 (I/O1), SV1.5
HC: IC5.13 (I/O2), SV1.7
HD: IC5.15 (I/O3), SV1.9
HE: IC5.16 (I/O4), SV1.11
HF: IC5.17 (I/O5), SV1.13
HG: IC5.18 (I/O6), SV1.15
HSEL: IC5.19 (I/O7), SV1.17
LA: IC4.11 (I/O0), SV1.4
LB: IC4.12 (I/O1), SV1.6
LC: IC4.13 (I/O2), SV1.8
LD: IC4.15 (I/O3), SV1.10
LE: IC4.16 (I/O4), SV1.12
LF: IC4.17 (I/O5), SV1.14
LG: IC4.18 (I/O6), SV1.16
LSEL: IC4.19 (I/O7), SV1.18
unnamed: CON3.4, IC4.25 (A8), IC5.25 (A8), QG1.8 (OUT)
PCH0: IC5.10 (A0), IC46.2 (A1)
PCH1: IC5.9 (A1), IC46.3 (A2)
PCH2: IC5.8 (A2), IC46.4 (A3)
PCH3: IC5.7 (A3), IC46.5 (A4)
PCH4: IC5.6 (A4), IC46.6 (A5)
PCH5: IC5.5 (A5), IC46.7 (A6)
PCH6: IC5.4 (A6), IC46.8 (A7)
PCH7: IC5.3 (A7), IC46.9 (A8)
PCL0: IC4.10 (A0), IC44.2 (A1)
PCL1: IC4.9 (A1), IC44.3 (A2)
PCL2: IC4.8 (A2), IC44.4 (A3)
PCL3: IC4.7 (A3), IC44.5 (A4)
PCL4: IC4.6 (A4), IC44.6 (A5)
PCL5: IC4.5 (A5), IC44.7 (A6)
PCL6: IC4.4 (A6), IC44.8 (A7)
PCL7: IC4.3 (A7), IC44.9 (A8)
VCC: C1.1, C2.1, C3.1, C4.1, C5.1, CON6.2, CON6.4, CON6.6, CON6.8, CON6.10, CON7.2, CON7.4, CON7.6, CON7.8, CON7.10, IC4.1 (VPP), IC4.2 (A12), IC4.21 (A10), IC4.23 (A11), IC4.24 (A9), IC4.26 (A13), IC4.27 (A14), IC4.28 (VCC), IC5.1 (VPP), IC5.2 (A12), IC5.21 (A10), IC5.23 (A11), IC5.24 (A9), IC5.26 (A13), IC5.27 (A14), IC5.28 (VCC), IC44.20 (VCC), IC46.20 (VCC), QG1.14 (VCC), SV1.1, SV1.2

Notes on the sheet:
Program Counter
Low
High

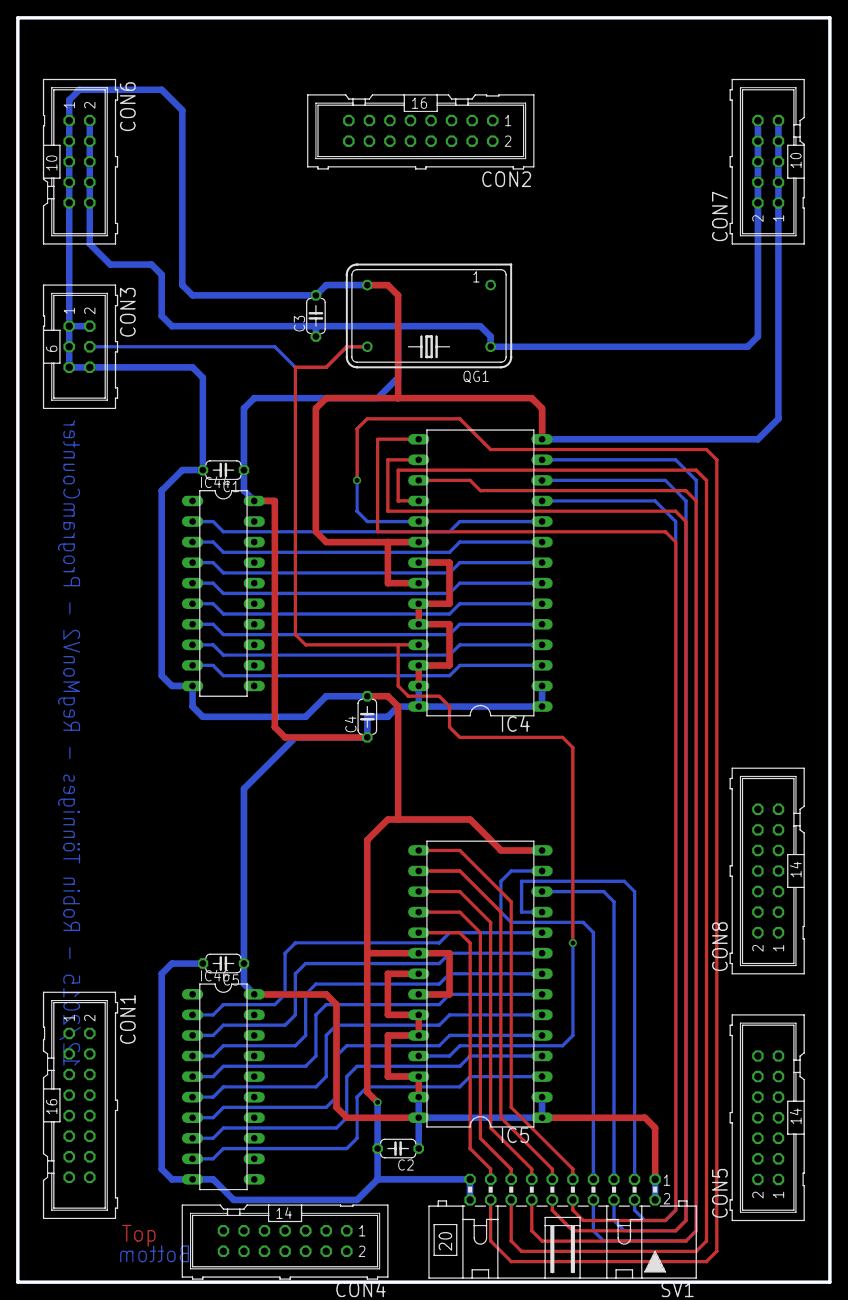
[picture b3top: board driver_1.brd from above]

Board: 2 copper layers, 100.3 x 156.2 mm, 19 parts (0 on the bottom side), 35 nets.
